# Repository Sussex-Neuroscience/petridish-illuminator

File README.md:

# petridish-illuminator
A simple PCB to illuminate petridishes

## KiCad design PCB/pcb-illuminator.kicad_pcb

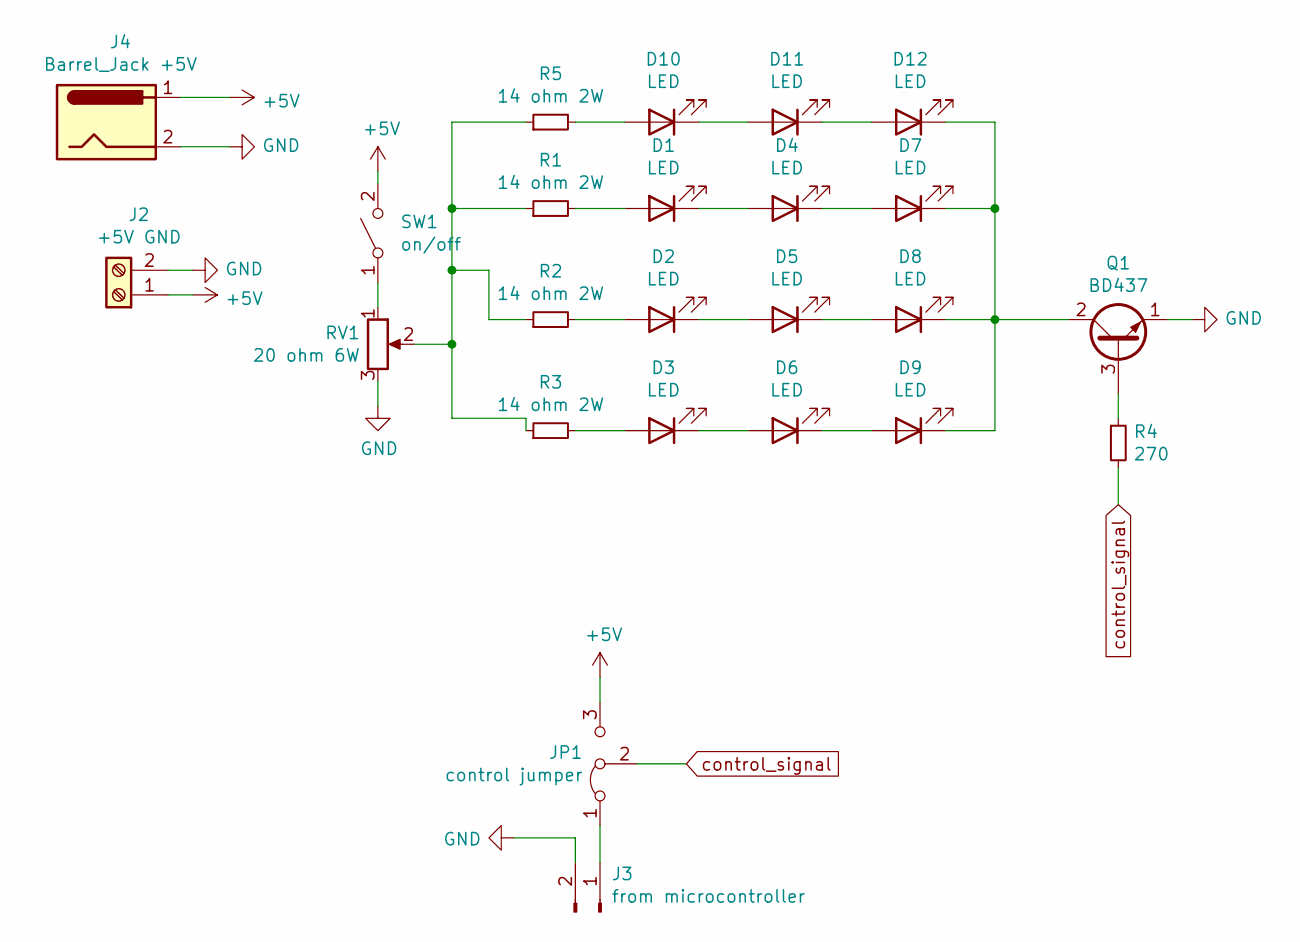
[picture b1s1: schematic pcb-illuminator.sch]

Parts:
D1, D2, D3, D4, D5, D6, D7, D8, D9, D10, D11, D12: LED; LED_D5.0mm
J2: +5V GND; TerminalBlock_Altech_AK300-2_P5.00mm
J3: from microcontroller; PinHeader_1x02_P2.54mm_Vertical
J4: Barrel_Jack +5V; BarrelJack_Horizontal
JP1: control jumper; PinHeader_1x03_P2.54mm_Vertical
Q1: BD437; TO-126-3_Vertical
R1, R2, R3, R5: 14 ohm 2W; R_Axial_DIN0411_L9.9mm_D3.6mm_P15.24mm_Horizontal
R4: 270; R_Axial_DIN0309_L9.0mm_D3.2mm_P12.70mm_Horizontal
RV1: 20 ohm 6W; Potentiometer_Bourns_3339W_Horizontal
SW1: on/off; PinHeader_1x02_P2.54mm_Vertical

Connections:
+5V: J2.1, J4.1, JP1.3 (B), SW1.2 (B)
GND: J2.2, J3.2, J4.2, Q1.1 (E), RV1.3
unnamed: D1.1 (K), D4.2 (A)
unnamed: D1.2 (A), R1.2
unnamed: D2.1 (K), D5.2 (A)
unnamed: D2.2 (A), R2.2
unnamed: D3.1 (K), D6.2 (A)
unnamed: D3.2 (A), R3.2
unnamed: D4.1 (K), D7.2 (A)
unnamed: D5.1 (K), D8.2 (A)
unnamed: D6.1 (K), D9.2 (A)
unnamed: D10.1 (K), D11.2 (A)
unnamed: D10.2 (A), R5.2
unnamed: D11.1 (K), D12.2 (A)
unnamed: D7.1 (K), D8.1 (K), D9.1 (K), D12.1 (K), Q1.2 (C)
unnamed: J3.1, JP1.1 (A)
unnamed: Q1.3 (B), R4.1
unnamed: R1.1, R2.1, R3.1, R5.1, RV1.2
unnamed: RV1.1, SW1.1 (A)
control_signal: JP1.2 (C), R4.2

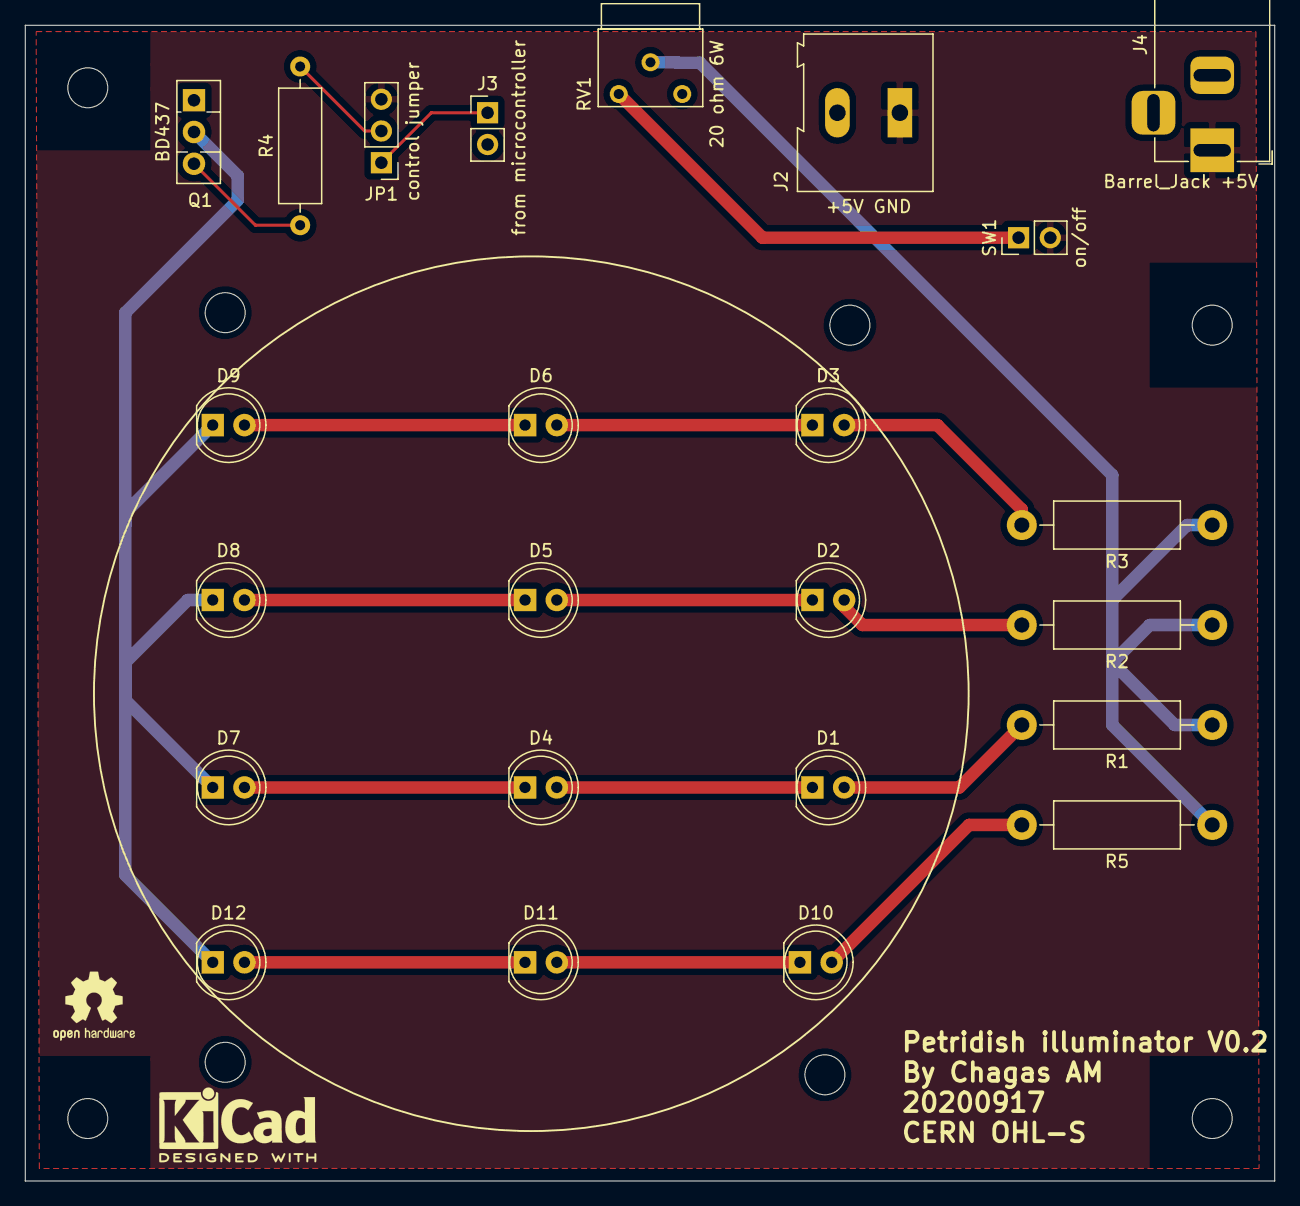
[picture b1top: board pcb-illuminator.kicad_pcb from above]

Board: 2 copper layers, 100.0 x 92.5 mm, 24 parts (0 on the bottom side), 20 nets.

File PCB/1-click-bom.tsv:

References	Qty	Description
D1, D4, D3, D6, D9, D7, D2, D5, D8	9	LED Light emitting diode D5.0mm
J1	1	USB C Receptacle USB2.0 2.0-only Type-C connector GCT USB4085
J2	1	Screw Terminal 01x02 +5V GND Generic screw terminal, single row, 01x02, script generated (kicad-library-utils/schlib/autogen/connector/) TerminalBlock Altech AK300-2 P5.00mm
J3	1	Conn 01x02 Male from microcontroller Generic connector, single row, 01x02, script generated (kicad-library-utils/schlib/autogen/connector/) PinHeader 1x02 P2.54mm Vertical
J4	1	Barrel Jack +5V DC BarrelJack Horizontal
JP1	1	Jumper 3 Bridged12 control jumper Jumper, 3-pole, pins 1+2 closed/bridged PinHeader 1x03 P2.54mm Vertical
Q1	1	BD433 4A Ic, 22V Vce, Power NPN Transistor, TO-126 TO-126-3 Vertical
R3, R1, R2	3	R Small 14 ohm 2W Resistor, small symbol Axial DIN0309 L9.0mm D3.2mm P5.08mm Vertical
R4	1	R Small 270 Resistor, small symbol Axial DIN0309 L9.0mm D3.2mm P5.08mm Vertical
RV1	1	R POT 20 ohm 6W Potentiometer Bourns 3339W Horizontal
SW1	1	SW SPST on/off Single Pole Throw (SPST) switch PinHeader 1x02 P2.54mm Vertical

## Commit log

2020-08-06 first board iteration and prep for kitspace
2020-09-17 move connectors, add another led row

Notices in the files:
PCB/pcb-illuminator.kicad_pcb:
CERN OHL-S
